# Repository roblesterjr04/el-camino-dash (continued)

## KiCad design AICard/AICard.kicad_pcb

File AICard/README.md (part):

# AI voice card

A **slot card** for the DigiDash rev 2 board: **80 × 60 mm**, standing on edge in a 2×15 slot, its right-angle header on the
bottom edge (`docs/hardware/accessory_ports.md`, rev 2 section). Requirements and design:
[`docs/hardware/ai_card.md`](../docs/hardware/ai_card.md). Firmware: [`firmware/ai_card/`](../firmware/ai_card/README.md)
(this card's ESP32-S3) and [`firmware/ai_agent/`](../firmware/ai_agent/README.md) (the assistant on the compute module).
It goes in **any slot**. On it:
- an **ESP32-S3-WROOM-1U-N16R8** (16 MB flash, 8 MB octal PSRAM; the IPEX version, because the radio is not used): CAN node,
  the I2S rail as a slave (microphone in, voice out), the wake word, the compute module's power switch
- a **2 × 20 female socket** (2.54 mm, 8.5 mm insulator) for the **compute module**, a Raspberry-Pi-header Linux board
  (reference: Radxa Zero 3W 8 GB with eMMC), held by two M2.5 standoffs
- a **TPS54560B buck** making the module's 5 V from **AUX 12 V** (slot pins 25–30), switched by the ESP32 through a P-FET
  (fail-safe: off whenever the ESP32 is off), with 470 µF bulk and a 220k / 47k sense of the AUX 12 V input
- a **74LVC125** that drives the rail's **RET** line only while the audio card grants it (enable pulled to *off*), 33 Ω in series
- an **MCP2562** CAN transceiver and an **AP7361C-33** 3.3 V regulator, both from the slot's 5 V
- **USB-C** (left edge) to the ESP32-S3's native USB, **BOOT** and **RESET** buttons, a **debug serial** header, two LEDs
  (module running, microphone open) and a **10k NTC** read by the ESP32

CAN node from its slot (`0x14 + (slot − 1)`), product `0x0007`. Firmware: `firmware/ai_card/`.

> ## Measure the compute module before ordering
>
> The module's size, header position and mounting holes on this card are **provisional**: they follow the Raspberry Pi Zero
> format, not a module in hand. The header map itself is the Raspberry Pi standard. Check, and edit the constants,
> then re-run the generators (see [Regenerating](#regenerating)):
>
> 1. **Pin 1 end and orientation of the header.** `J2_PIN1` in `generate/gen_pcb.py` (pin 1 at the left end, odd pins in the
>    upper row). If the module's pin 1 is at the other end the 5 V pins (2, 4) move to the other side of the card.
> 2. **Module outline** `MOD_X0, MOD_Y0, MOD_W, MOD_H` (65 × 30 mm, header 5 mm in from its lower edge). Nothing taller than
>    about 7 mm may stand inside it (the 470 µF is outside); check the module's bottom-side parts against the 8.5 mm socket.
> 3. **Mounting holes** `MOUNT_HOLES` (two of the module's far corners, 3.5 mm in; M2.5, 2.7 mm holes). Fit the standoffs
>    before judging: a 2×20 socket alone will walk out of a vibrating dash.
> 4. **Which header pins the module really uses** (`HEADER_NETS` in `generate/gen_sch.py`): UART on 8 / 10, ALIVE on 29,
>    SHUTDOWN_REQ on 31, ATTN on 33. Check that the module **accepts its 5 V supply on header pins 2 / 4** (it does on a Pi
>    Zero; confirm for the module in hand, and that nothing else powers it: no USB-C power while it sits on the card), which UART
>    pins 8 / 10 are on it and the device-tree overlay that enables it (`[link] port` in the agent's config), and that the GPIOs are
>    3.3 V.
> 5. **Height:** 8.5 mm socket + module + its heatsink must stay under the **20 mm** parts-side limit.
> 6. **Power:** the module's idle and peak current from the bench (the buck is 5 A; the design assumes 3 A peak).

| Files | |
| --- | --- |
| `AICard.kicad_sch` / `.kicad_pcb` / `.kicad_pro` | The card: 80 × 60 mm, 4 layers, parts on the front only. Generated with KiCad 7.0.11; the files were upgraded to KiCad 10 format on 2026-11-22 |
| `AICard_BOM.csv` | Bill of materials (`generate/gen_bom.py`) |
| `generate/` | `gen_sch.py`, `gen_pcb.py`, `gen_bom.py`, `drc.py`, `sexp.py`; `refs.json` is written by `gen_sch.py`. Copied from `LTECard/generate/` and adapted. Every footprint is stock KiCad, so there is no `.pretty` library |

## What's on it

```
AUX 12 V (pins 25-27) ─ 3 × 2.2 µF 100 V ─ TPS54560B (400 kHz) ─ 6.8 µH ─ MOD_5V ─┬─ 3 × 47 µF
AUX GND  (pins 28-30) ─────── all of the buck's grounds ─┘                         └─ 470 µF ─ socket pins 2, 4 (5 V)
                              socket GND pins (6, 9, 14, 20, 25, 30, 34, 39) = AUX_GND
AUX 12 V ─ 220k / 47k ─ GPIO5 (AUX present: the buck's INPUT; its output is off until the firmware has seen this)
Enable:  AUX12 ─ Q1 (P-FET) ─ 442k / 90.9k divider (starts at ~6.5 V, 5.1 V zener) ─ buck EN
         Q1 gate: 47k to AUX12, 47k to Q2; Q2 (N-FET) gate: GPIO11 through 1k, 100k pull-down. ESP32 off / in reset / unpowered = buck off
+5 V (pins 1, 2) ─ AP7361C-33 ─ +3V3 ─ ESP32-S3, MCP2562 VIO, 74LVC125, thermistor divider
ESP32-S3 UART1  TX GPIO41 ─ 1k ─► module RXD (socket 10)     RX GPIO42 ◄─ 1k ─ module TXD (socket 8)
         SHUT GPIO12 ─ 1k ─► socket 31   ALIVE GPIO13 ◄─ 1k ─ socket 29   ATTN GPIO14 ◄─► 1k ─ socket 33   (100k pull-downs on the ESP32 side)
I2S rail (slave): slot 15 BCK ─ 100 R ─ GPIO6   16 WS ─ 100 R ─ GPIO7   17 MIC ─ 100 R ─ GPIO15
         GPIO16 (RET data) ─► 74LVC125 gate 1 (/OE = GPIO17, 100k pull-up: off at power-up) ─ 33 R ─► slot 18 RET
CAN: GPIO9 TX / GPIO10 RX ── MCP2562 (VDD 5 V, VIO 3.3 V, STBY low, no termination) ── slot pins 5 / 6
Slot ID (pin 11): 10k to 3.3 V here, the slot's resistor to GND on the main board ──► GPIO4 (ADC1)
USB-C D+ / D- ── USBLC6-2SC6 ── GPIO20 / GPIO19 (native USB); CC1 / CC2 5.1k to GND; VBUS only to the clamp
```

### ESP32-S3 pins

| GPIO | Function | GPIO | Function |
| --- | --- | --- | --- |
| 41 / 42 | UART1 TX / RX to the module | 9 / 10 | CAN TX / RX (through 1k) |
| 11 | BUCK_ON (module's buck enable) | 4 | Slot ID (ADC1_CH3) |
| 12 | SHUTDOWN_REQ out | 5 | AUX 12 V present (ADC1_CH4): 2.1 V at 12 V |
| 13 | ALIVE in | 8 | NTC (ADC1_CH7) |
| 14 | ATTN (spare) | 1 / 2 | LED module / LED microphone |
| 6 / 7 / 15 | rail BCK / WS / MIC in | 19 / 20 | USB D− / D+ |
| 16 / 17 | RET data out / RET buffer enable (low = drive) | 43 / 44 | TXD0 / RXD0, debug serial J3 |
| 0 | BOOT button (strap) | EN | RESET button, 10k / 1 µF |

Not used: the strapping pins GPIO3, 45, 46 (and GPIO0 except for BOOT), the flash and octal-PSRAM pins GPIO26–37, GPIO18, 21, 38–40, 47, 48.
`firmware/ai_card/src/ai_pins.h` repeats this table; keep them in step.

### Grounds: AUX GND is not GND

As on the LTE card: on the main board AUX GND meets GND only at NT1, so this card does **not** join them. The buck, the 470 µF and the
module's return are on AUX_GND (its own pours on F, In2 and B over the buck area); the ESP32, CAN, USB, the rail and the 3.3 V
regulator are on GND (In1 is a solid GND plane under the whole card). Only logic crosses, through 1k resistors. On the bench a card
powered without the main board needs AUX GND and GND joined at the supply.

## Slot connector (J1)

| Pins | Signal | Used |
| --- | --- | --- |
| 1 / 2 | +5 V | ESP32-S3, CAN, 3.3 V regulator |
| 3 / 4, 7, 19 / 20 | GND | logic ground |
| 5 / 6 | CANH / CANL | MCP2562 |
| 11 | slot ID | 10k to 3.3 V, GPIO4 |
| 15 / 16 / 17 | I2S BCK / WS / MIC | inputs through 100 Ω |
| 18 | I2S RET | 74LVC125 and 33 Ω: a 3-state output, never driven without the audio card's grant |
| 25 / 26 / 27 | AUX 12 V | the module's buck |
| 28 / 29 / 30 | AUX GND | the buck and the module's return |
| 8, 9, 10, 12–14, 21–24 | switched / constant 12 V, 3.3 V, WAKE, LAMP, REV, audio bus, MCLK | not connected |

| Other connectors | | |
| --- | --- | --- |
| J2 | Compute module, 2 × 20 female, 8.5 mm | Raspberry Pi 40-pin map: 5 V on 2 / 4, GND on 6 / 9 / 14 / 20 / 25 / 30 / 34 / 39, UART 8 / 10, ALIVE 29, SHUTDOWN_REQ 31, ATTN 33 |
| J3 | debug serial, 1 × 3 right angle, left edge | 1 GND, 2 TX0 (to the adapter's RX), 3 RX0. 3.3 V logic, not a supply |
| J4 | USB-C (GCT USB4105, horizontal), left edge | native USB: flash and serial console. The card is powered from the slot |
| SW1 / SW2 | RESET / BOOT, top edge | Flash: hold BOOT, tap RESET (only needed if the USB-JTAG is not answering) |
| H1 / H2 | M2.5 holes for the module's standoffs | provisional positions |

## Board

- **Outline:** 80 × 60 mm, no card-mounting holes (the slot and the case hold it); two M2.5 holes for the module only.
- **Slot header (J1):** placed exactly as on the audio and LTE cards (`PinHeader_2x15_P2.54mm_Horizontal`, pin 1 17.78 mm right of
  the centre, the pins counting to the left, its body on the bottom edge); `gen_pcb.py` checks the orientation from the pads.
- **Middle:** the module's socket across the card (pin 1 at the left); the module hangs over the upper half of the card,
  8.5 mm up. **Under it** (all lower than 7 mm): the ESP32-S3-1U at the left, the buttons and thermistor, LEDs, resistors.
- **Left edge:** LEDs, USB-C (plug facing out), the debug header (pins out of the edge). **Top edge:** RESET / BOOT.
- **Bottom:** the buck by the AUX pins (25–30), the 470 µF beside it (10 mm tall, so outside the module's shadow), the RET
  buffer by the rail pins (15–18), the CAN transceiver and the 3.3 V regulator by pins 1–6.
- **Back:** nothing (it faces the next card; the 2.5 mm allowance is not used).
- **Layers:** F signal, In1 solid GND plane, In2 signal / pours, B signal. 0.2 mm tracks, 0.13 mm clearance, 0.6 / 0.3 mm vias.
  Net classes as on the LTE card: Power 0.3 mm (GND, +5V, +3V3); Aux 0.8 mm / 0.2 mm (AUX12); Mod5V 1.0 mm / 0.2 mm (MOD_5V); AuxGnd 0.8 mm / 0.2 mm
  (AUX_GND); Switch 1.0 mm / 0.2 mm (BUCK_SW).
- **No antenna:** the -1U module's IPEX connector is left empty; Wi-Fi is the compute module's (its own antenna).

## Status

**Schematic: done** (78 parts). **PCB: placed and routed** by `gen_pcb.py` (2026-10-04): 80 × 60 mm, 4 layers, 78 footprints,
747 tracks and 635 vias (558 of them GND stitching), Freerouting 2.4.1 plus the script's own steps, no hand edits.
DRC (KiCad 7.0.11): **0 errors, 0 unconnected.** Warnings only: 78 "library not in the library table" (the project has no
`fp-lib-table`, as on the LTE card), 20 silkscreen past the edge (J1, J3 and J4 stick out of the outline on purpose), 3 silkscreen
clipped by mask, 2 silkscreen overlaps. **Not ordered.** Merged to main on 2026-11-22; the BOM CSV was regenerated then (the committed one predated the
220k / 47k AUX sense divider and listed 22k / 33k, which would have put about 7 V on GPIO5). Fab files: `fab/` (`python3 ../tools/fab_export.py AICard`).

**KiCad 10 pass (2026-11-22).** Both files upgraded with `kicad-cli sch upgrade` / `pcb upgrade`; nothing on the board moved.
- **ERC** (KiCad 10.0.2): 0 errors, 409 warnings: 396 endpoints off grid, 13 library notes (the `AICard` symbol nickname is not in a
  library table; J4's and the LEDs' symbols differ from KiCad 10's copies).
- **DRC with the schematic parity check** (`generate/drc.py`, now kicad-cli as on the other cards): 0 errors, 0 unconnected.
  Warnings: 68 footprints differ from KiCad 10's library copies, 68 *Description* fields set in the schematic only, 20 silkscreen past
  the edge (J1, J3, J4, on purpose), 5 silkscreen over copper, 2 silkscreen overlaps. Parity otherwise clean: every part, value and net matches.
- **Mask dams:** `tools/mask_dams.py` narrowed J4's eight 0.5 mm-pitch signal pads to 0.28 mm (0.22 mm gaps); zones refilled.
- **AP7361C-33E pinout checked** against the Diodes datasheet: suffix E is SOT223 (ER is the reversed SOT223R), pin 1 IN, 2 GND
  (tab), 3 OUT, as drawn. ConsoleBoardRS uses the same part and pinout.
- **Power tracks** measured in the routed board (the 5 V pre-route was blocked and the router laid them): MOD_5V 1.0 mm on F.Cu
  and B.Cu (a 0.8 mm stub at a pad), AUX12 and AUX_GND 0.8 mm, BUCK_SW 1.0 mm, the slot +5 V 0.3 mm (it feeds only the ESP32 side).
- **Fab files** re-exported with KiCad 10 (`fab/`, inner layers now `.g1` / `.g2`, plus a JLC CPL).

What has **not** been checked, and what to do about it before ordering:
- **The compute module** (size, header end, mounting holes, which pins it powers from): see the box at the top.
- **The buck** is the main board's circuit with a smaller inductor and the 470 µF at the load; its loop was not simulated. Check L1's
  ratings (Isat ≥ 5 A, Irms ≥ 3 A) and the compensation with TI WEBENCH or a load-step test on the real module.
- **J4 (the GCT USB4105)**: its own locating hole is 0.194 mm from pad B12, so the project's minimum hole clearance is set to
  0.19 mm instead of 0.25 mm; confirm the fab's limit. Only the A4 / B9 VBUS contacts are wired (the others sit 4.8 mm away across the
  signal pads, and VBUS powers nothing here).
- **Thermal**: nothing has been measured; the design relies on the two-step throttle in the firmware (`docs/hardware/ai_card.md`).
- **AUX budget (changed on the main board after this card was drawn).** Since 2026-10-19 DigiDash2's AUX 12 V is sized for
  about **3 A for all slots together** (5 A fuse; it was 10 A). This card's 3 A peak at 5 V is about 1.4 A from 12 V, and the
  LTE card's modem buck about 1 A: both fit, with little margin. Measure the module's peak before adding another AUX user.
- **The module's UART on header pins 8 / 10** may be its Linux debug console (on Radxa Zero 3 boards it usually is, at
  1.5 Mbaud): either turn the console off in the module's image or move the link to another UART. Confirm on the module.
- **Slot numbering was fixed on the main board on 2026-10-19** (`accessory_ports.md`, Numbering). The card side did not change
  and J1 is placed as on the audio and LTE cards, so this card should mate; confirm in KiCad's 3D viewer with DigiDash2.
- **No PCBWay BOM yet** (`fab/pcbway/`, as on the other cards). Every part is SMD except J1–J3, which PCBWay can fit too.
- **Pin 1 of J1** against the main board's slot, and the USB-C and debug header against the case, in KiCad's 3D viewer.

## Regenerating

**The generators still write KiCad 7 format** (`gen_sch.py`, `gen_pcb.py`): after a regeneration run `kicad-cli sch upgrade` and
`kicad-cli pcb upgrade` on the two files, then `tools/mask_dams.py AICard` and `gen_pcb.py --fill`. `--fill` runs on KiCad 10's
Python (`$KIPY`); the full place-and-route has only been run on KiCad 7.

KiCad's stock libraries and `kicad-cli`, a Python with `pcbnew` and `numpy`, and Freerouting (Java; **2.4.1 needs Java 25** and
runs with `--gui.enabled=false`; 1.9.0 with Java 17+ also worked for the LTE card). This card was generated with KiCad
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
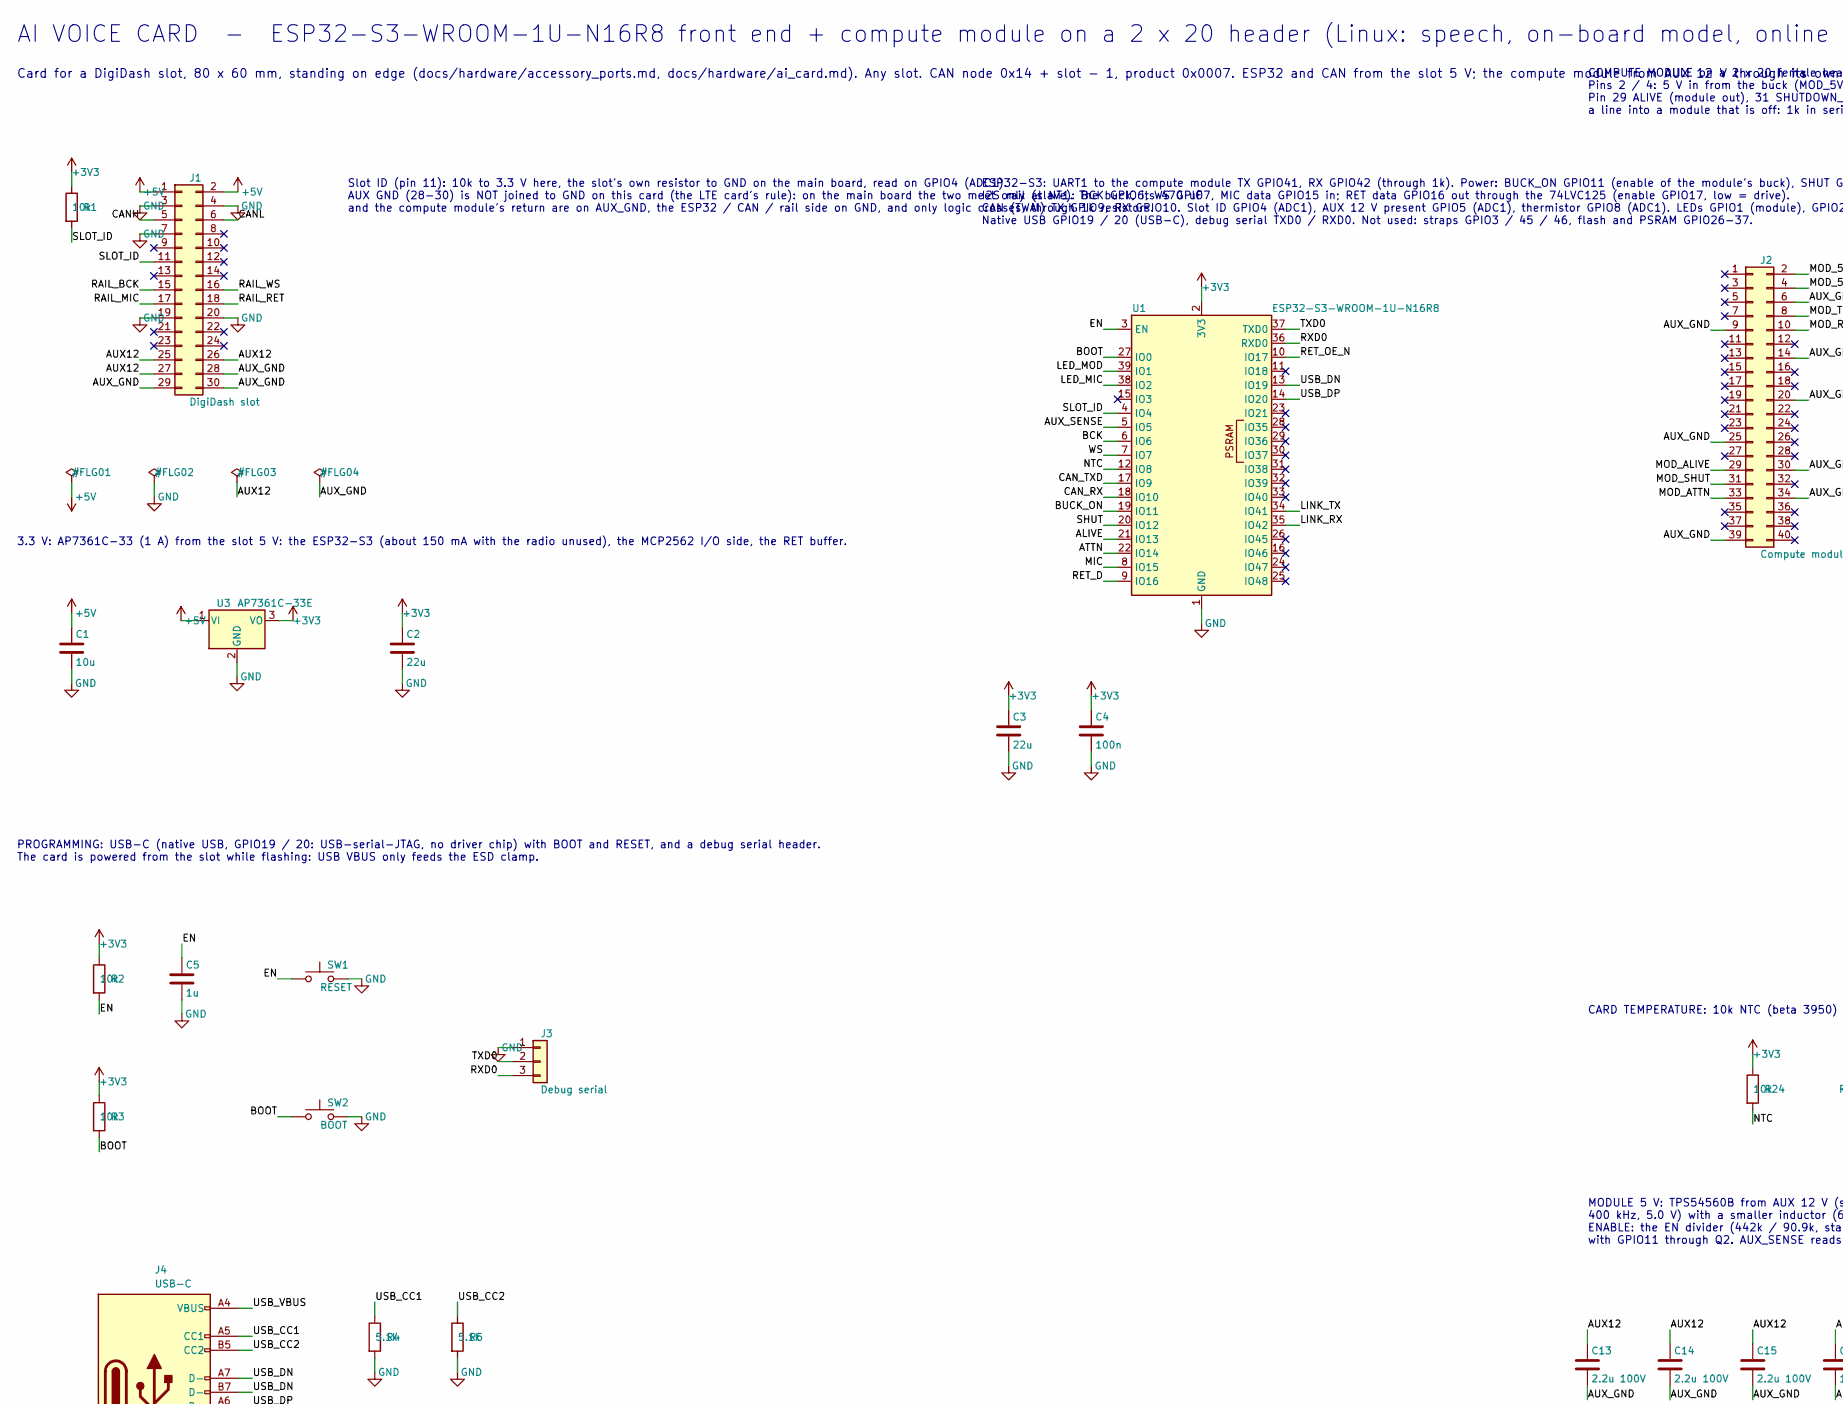
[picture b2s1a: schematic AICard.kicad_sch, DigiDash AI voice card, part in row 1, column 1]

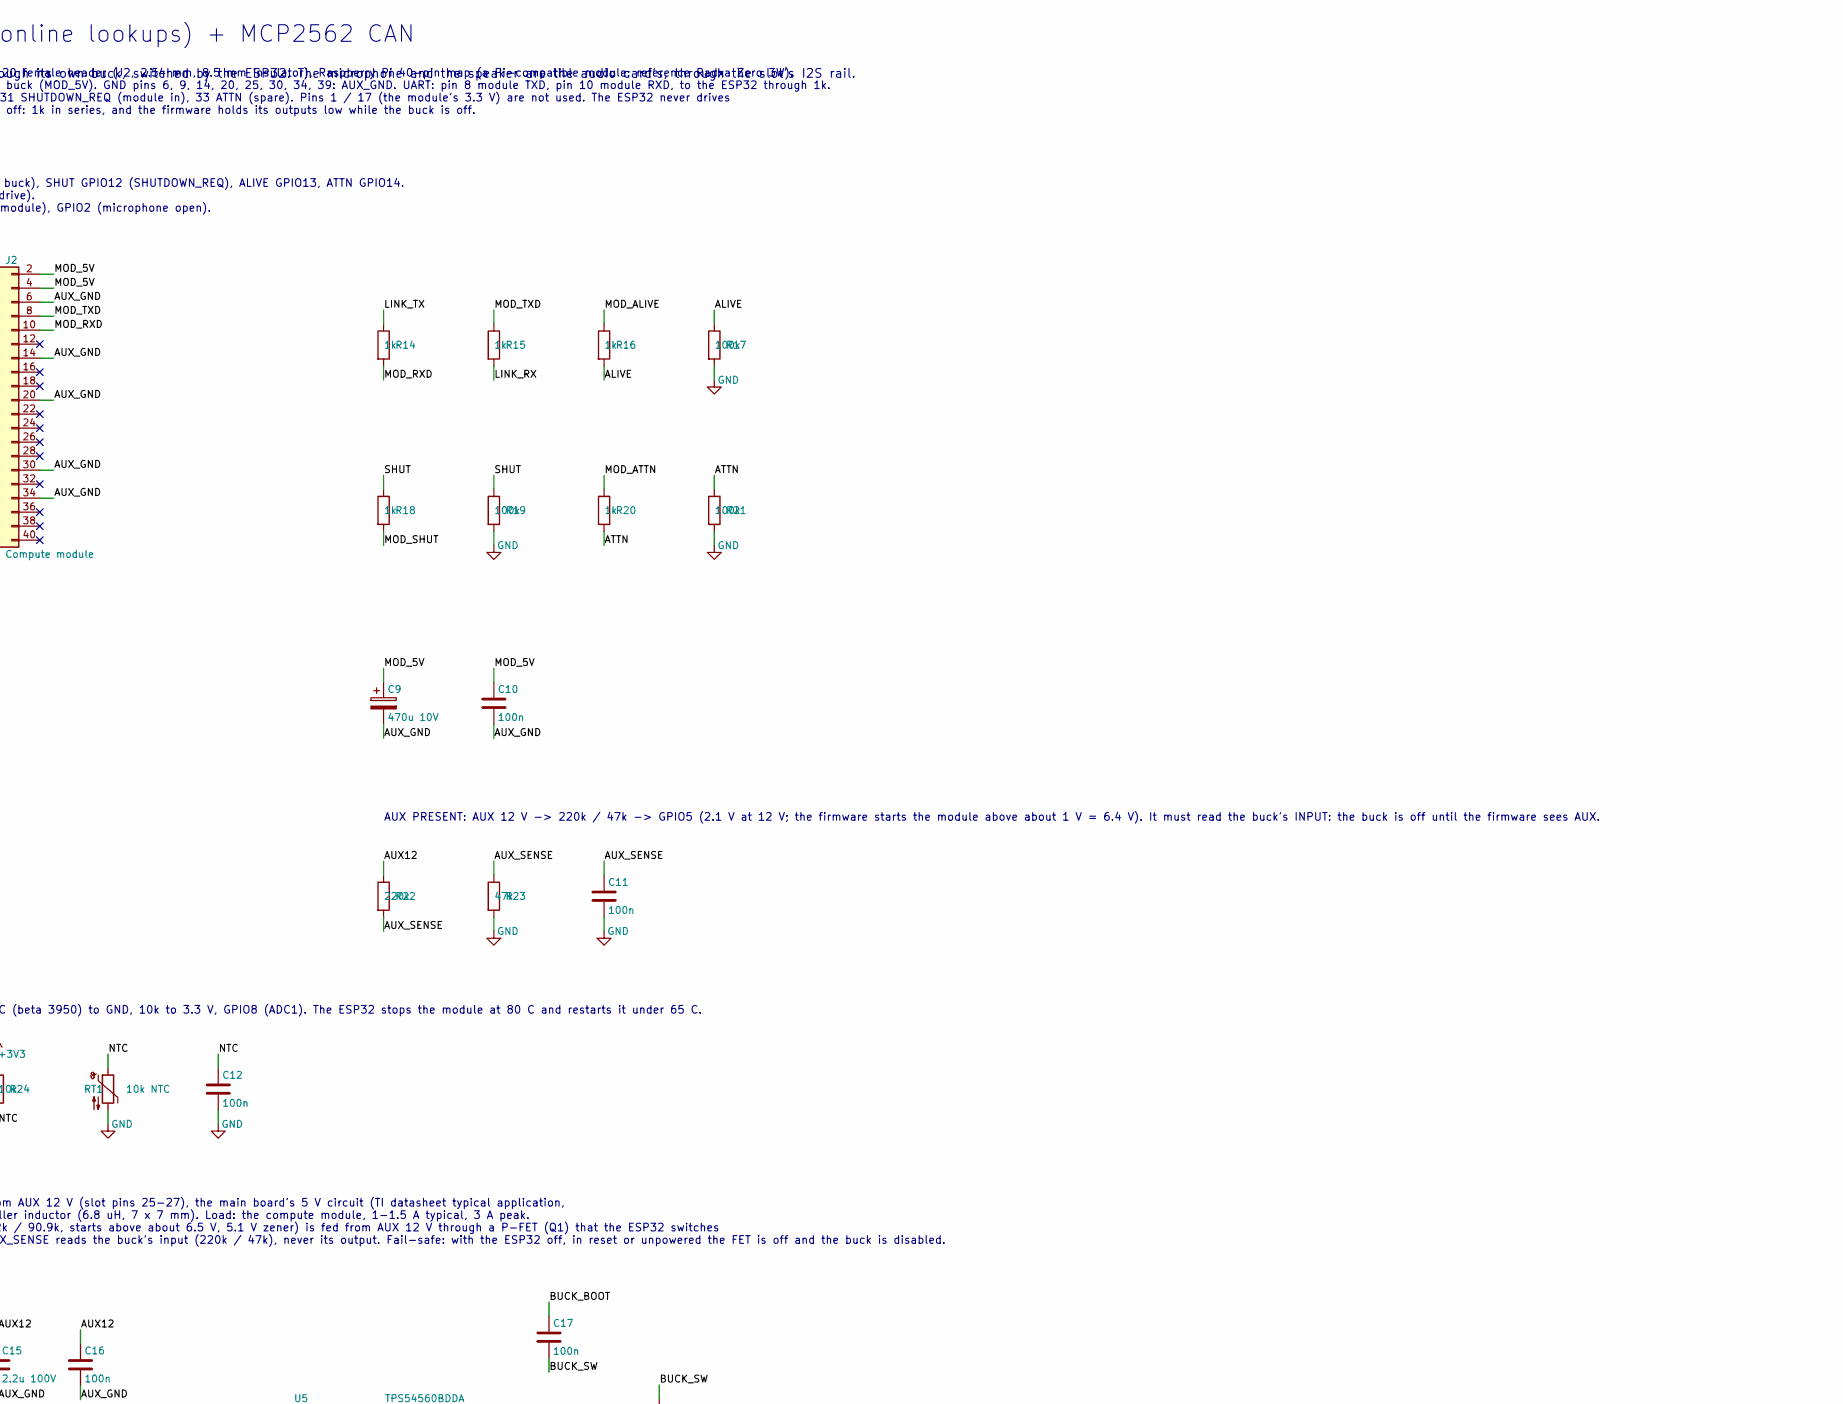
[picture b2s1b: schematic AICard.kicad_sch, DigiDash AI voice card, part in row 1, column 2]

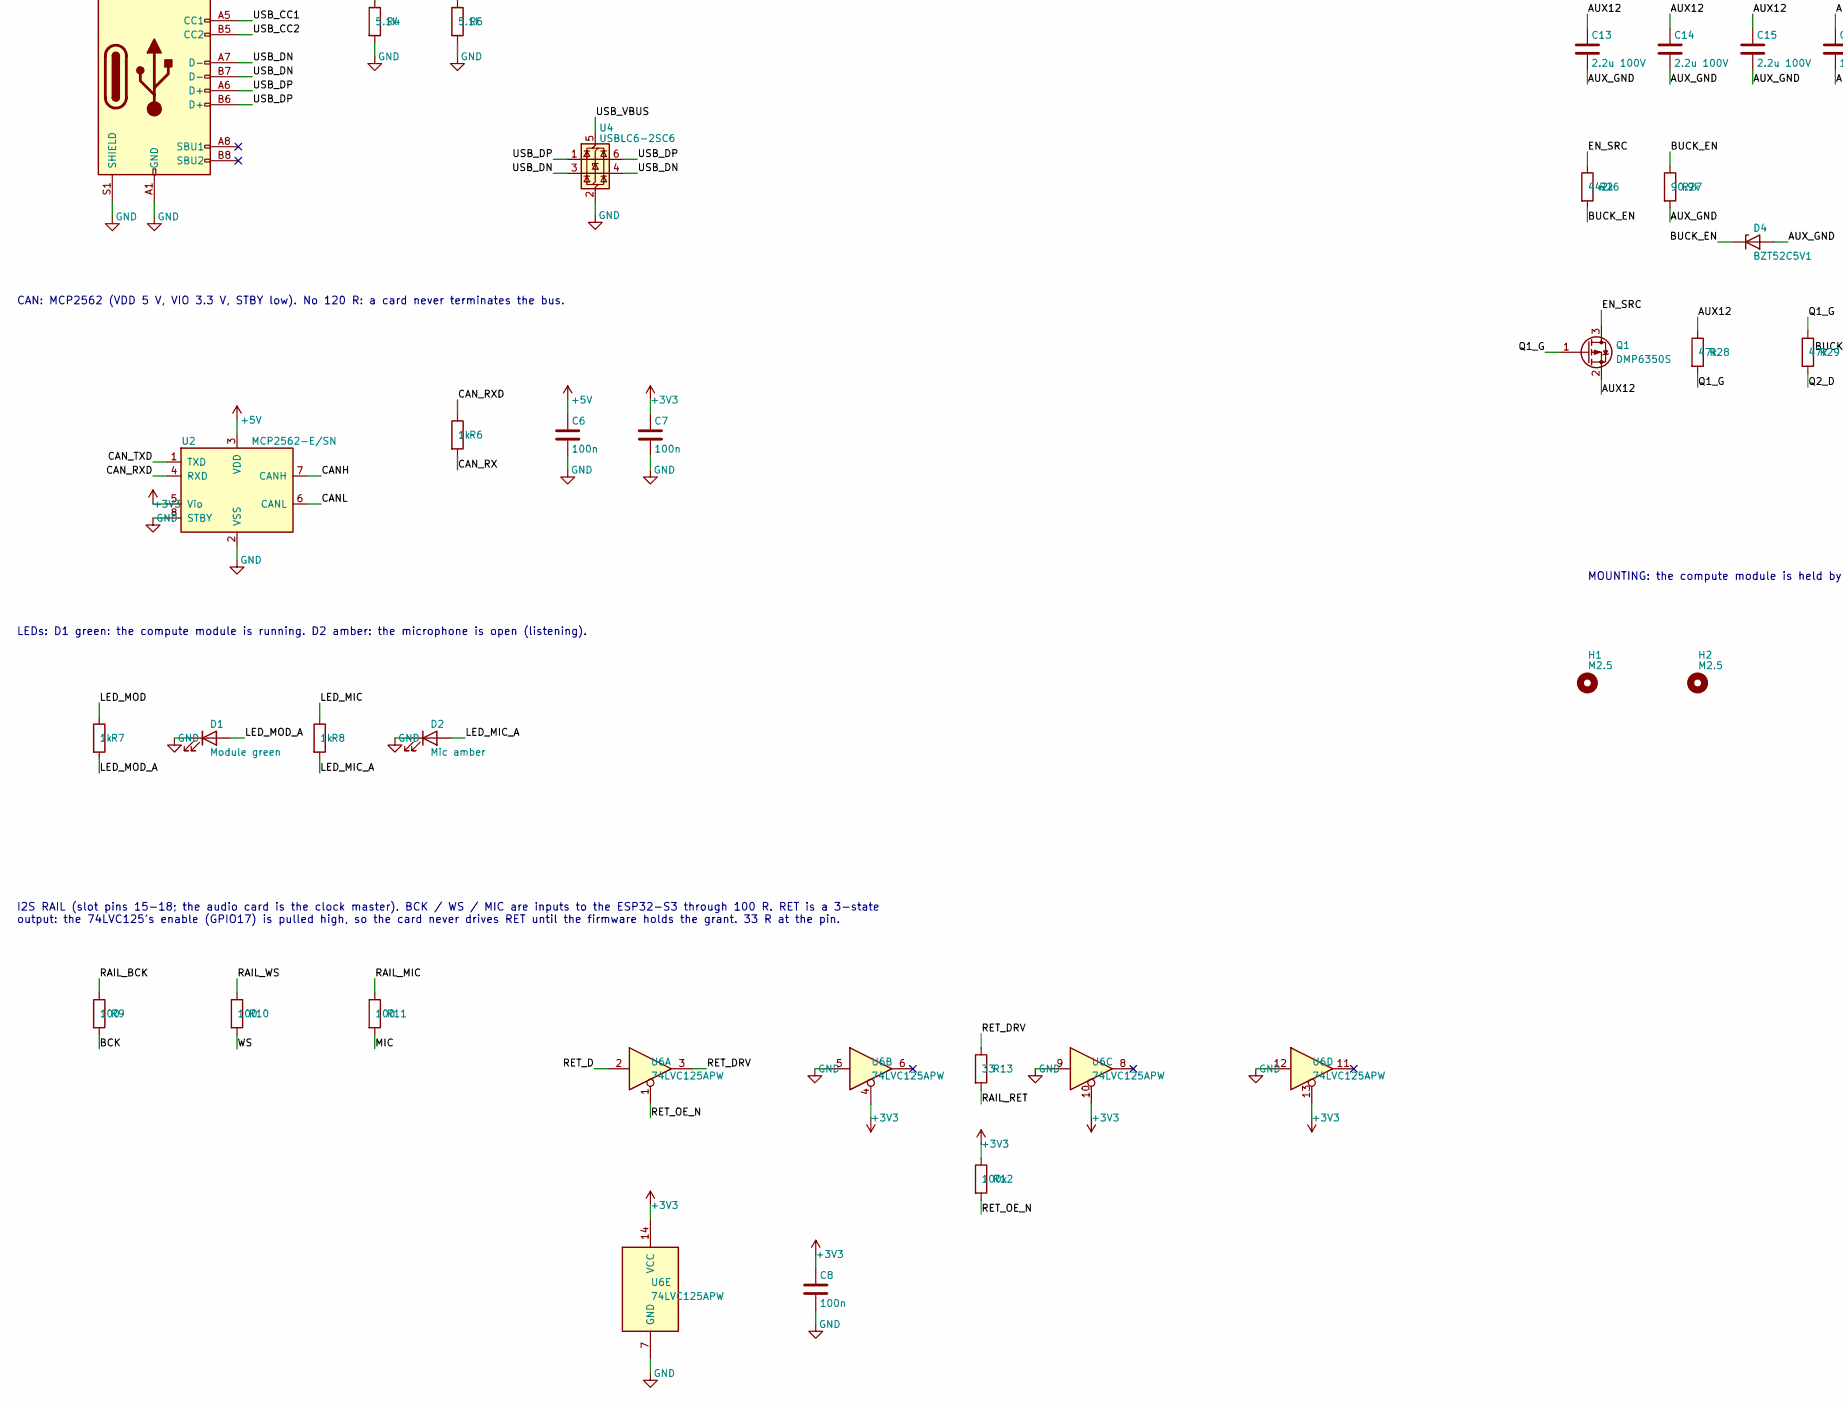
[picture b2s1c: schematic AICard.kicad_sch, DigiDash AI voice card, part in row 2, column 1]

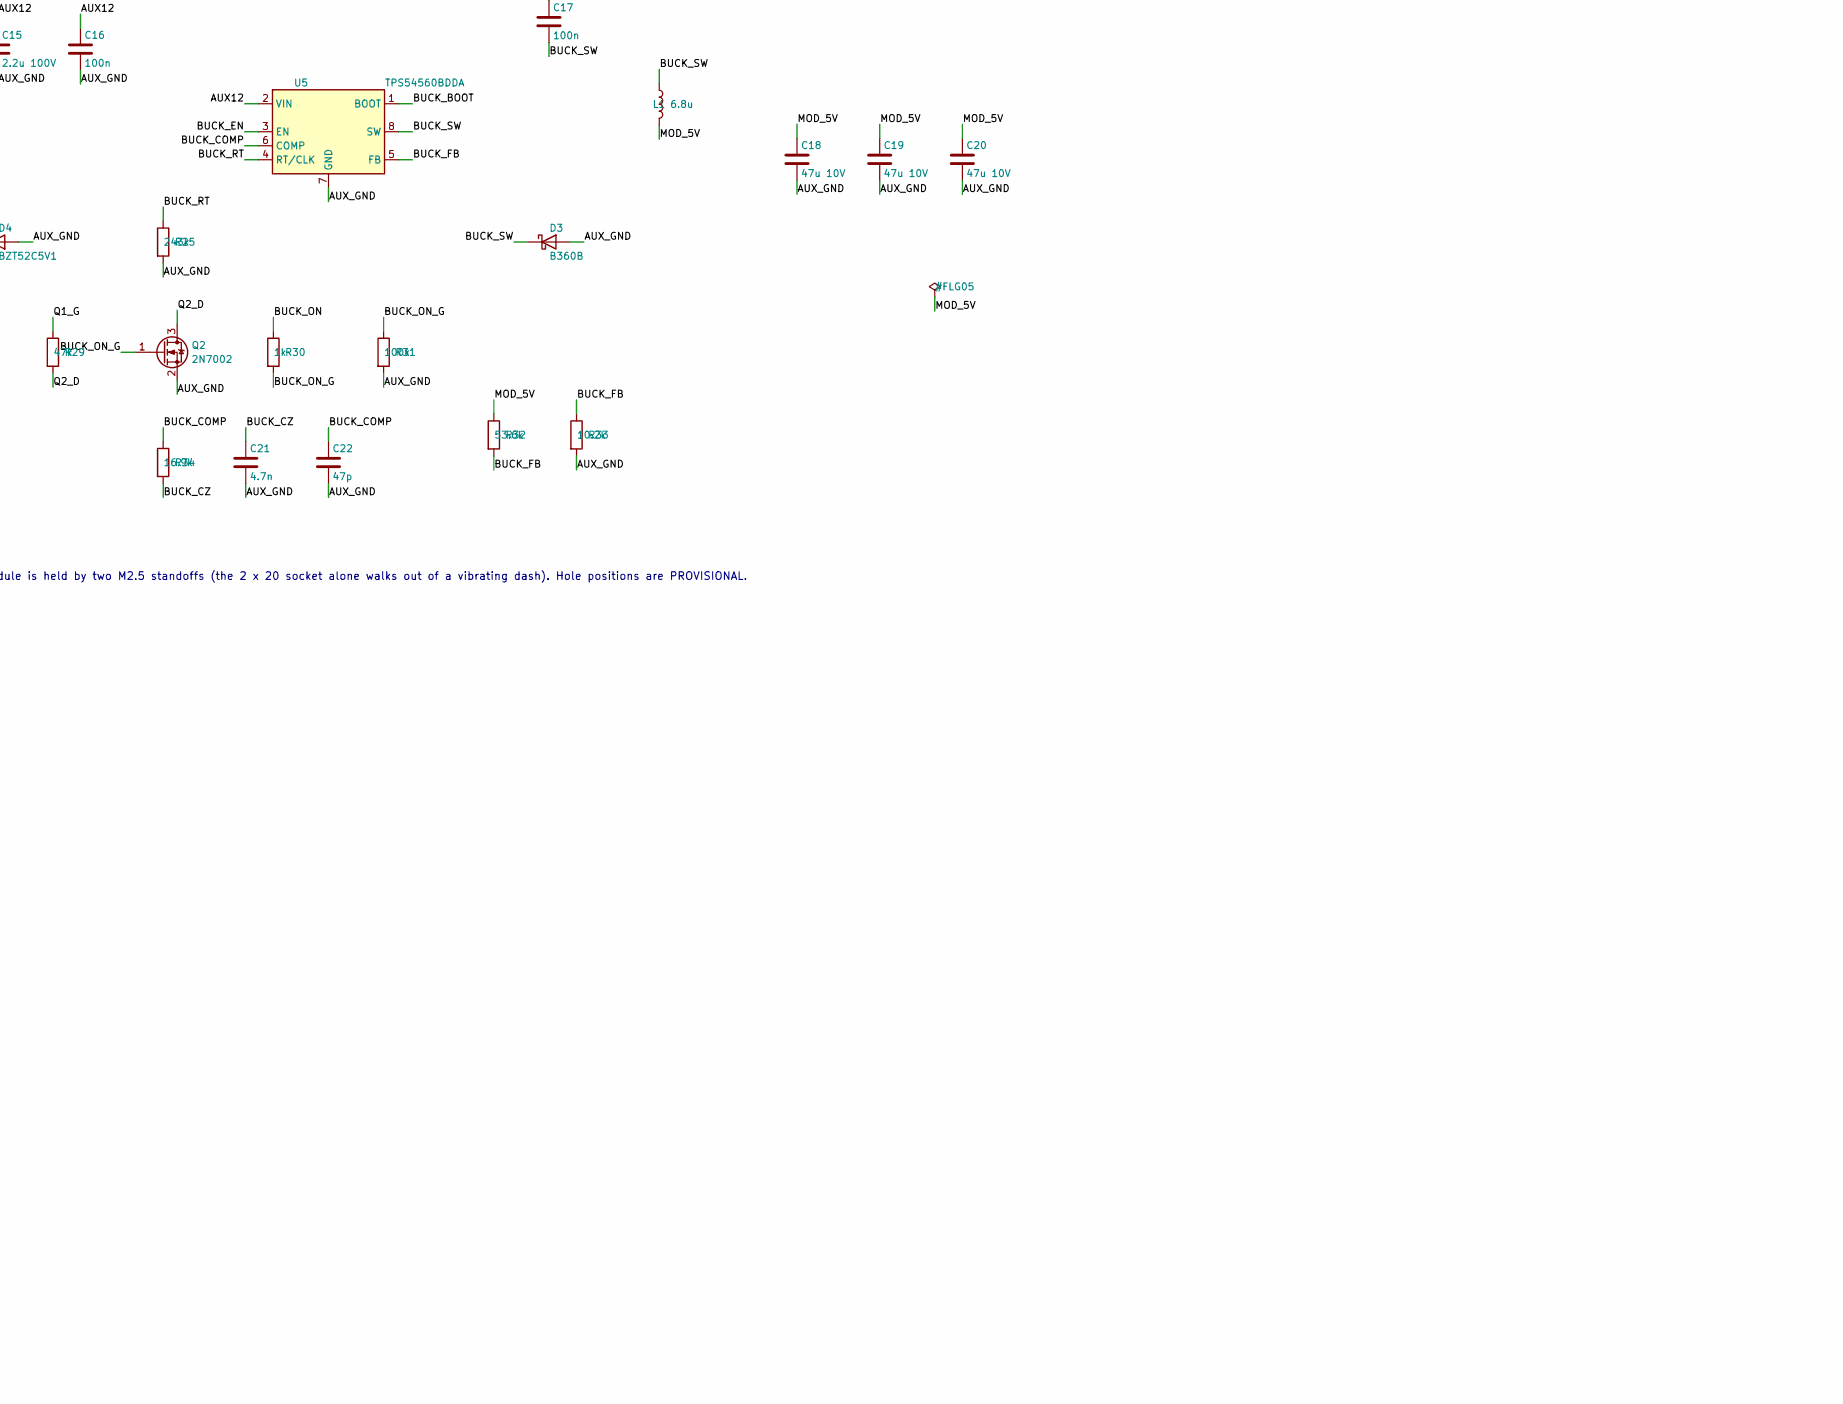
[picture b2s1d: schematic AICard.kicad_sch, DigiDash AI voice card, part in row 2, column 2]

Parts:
C1: 10u; C_0805_2012Metric
C2, C3: 22u; C_0805_2012Metric
C4, C6, C7, C8, C10, C11, C12, C17: 100n; C_0603_1608Metric
C5: 1u; C_0603_1608Metric
C9: 470u 10V; CP_Elec_8x10
C13, C14, C15: 2.2u 100V; C_1210_3225Metric
C16: 100n; C_0805_2012Metric
C18, C19, C20: 47u 10V; C_1210_3225Metric
C21: 4.7n; C_0603_1608Metric
C22: 47p; C_0603_1608Metric
D1: Module green; LED_0603_1608Metric
D2: Mic amber; LED_0603_1608Metric
D3: B360B; D_SMB
D4: BZT52C5V1; D_SOD-123
H1, H2: M2.5; MountingHole_2.7mm_M2.5
J1: DigiDash slot; PinHeader_2x15_P2.54mm_Horizontal
J2: Compute module; PinSocket_2x20_P2.54mm_Vertical
J3: Debug serial; PinHeader_1x03_P2.54mm_Horizontal
J4: USB-C; USB_C_Receptacle_GCT_USB4105-xx-A_16P_TopMnt_Horizontal
L1: 6.8u; L_Bourns_SRP7028A_7.3x6.6mm
Q1: DMP6350S; SOT-23
Q2: 2N7002; SOT-23
R1, R2, R3, R24: 10k; R_0603_1608Metric
R4, R5: 5.1k; R_0603_1608Metric
R6, R7, R8, R14, R15, R16, R18, R20, R30: 1k; R_0603_1608Metric
R9, R10, R11: 100; R_0603_1608Metric
R12, R17, R19, R21, R31: 100k; R_0603_1608Metric
R13: 33; R_0603_1608Metric
R22: 220k; R_0603_1608Metric
R23, R28, R29: 47k; R_0603_1608Metric
R25: 243k; R_0603_1608Metric
R26: 442k; R_0603_1608Metric
R27: 90.9k; R_0603_1608Metric
R32: 53.6k; R_0603_1608Metric
R33: 10.2k; R_0603_1608Metric
R34: 16.9k; R_0603_1608Metric
RT1: 10k NTC; R_0603_1608Metric
SW1: RESET; SW_SPST_PTS810
SW2: BOOT; SW_SPST_PTS810
U1: ESP32-S3-WROOM-1U-N16R8; ESP32-S3-WROOM-1U
U2: MCP2562-E/SN; SOIC-8_3.9x4.9mm_P1.27mm
U3: AP7361C-33E; SOT-223-3_TabPin2
U4: USBLC6-2SC6; SOT-23-6
U5: TPS54560BDDA; TI_SO-PowerPAD-8_ThermalVias
U6: 74LVC125APW; TSSOP-14_4.4x5mm_P0.65mm

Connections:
+3V3: C2.1, C3.1, C4.1, C7.1, C8.1, R1.1, R2.1, R3.1, R12.1, R24.1, U1.2 (3V3), U2.5 (Vio), U3.3 (VO), U6.4, U6.10, U6.13, U6.14 (VCC)
+5V: C1.1, C6.1, J1.1, J1.2, U2.3 (VDD), U3.1 (VI)
/ALIVE: R16.2, R17.1, U1.21 (IO13)
/ATTN: R20.2, R21.1, U1.22 (IO14)
/AUX12: C13.1, C14.1, C15.1, C16.1, J1.25, J1.26, J1.27, Q1.2 (S), R22.1, R28.1, U5.2 (VIN)
/AUX_GND: C9.2, C10.2, C13.2, C14.2, C15.2, C16.2, C18.2, C19.2, C20.2, C21.2, C22.2, D3.2 (A), D4.2 (A), J1.28, J1.29, J1.30, J2.6, J2.9, J2.14, J2.20, J2.25, J2.30, J2.34, J2.39, Q2.2 (S), R25.2, R27.2, R31.2, R33.2, U5.7 (GND), U5.9 (GND)
/AUX_SENSE: C11.1, R22.2, R23.1, U1.5 (IO5)
/BCK: R9.2, U1.6 (IO6)
/BOOT: R3.2, SW2.1, U1.27 (IO0)
/BUCK_BOOT: C17.1, U5.1 (BOOT)
/BUCK_COMP: C22.1, R34.1, U5.6 (COMP)
/BUCK_CZ: C21.1, R34.2
/BUCK_EN: D4.1 (K), R26.2, R27.1, U5.3 (EN)
/BUCK_FB: R32.2, R33.1, U5.5 (FB)
/BUCK_ON: R30.1, U1.19 (IO11)
/BUCK_ON_G: Q2.1 (G), R30.2, R31.1
/BUCK_RT: R25.1, U5.4 (RT/CLK)
/BUCK_SW: C17.2, D3.1 (K), L1.1, U5.8 (SW)
/CANH: J1.5, U2.7 (CANH)
/CANL: J1.6, U2.6 (CANL)
/CAN_RX: R6.2, U1.18 (IO10)
/CAN_RXD: R6.1, U2.4 (RXD)
/CAN_TXD: U1.17 (IO9), U2.1 (TXD)
/EN: C5.1, R2.2, SW1.1, U1.3 (EN)
/EN_SRC: Q1.3 (D), R26.1
/LED_MIC: R8.1, U1.38 (IO2)
/LED_MIC_A: D2.2 (A), R8.2
/LED_MOD: R7.1, U1.39 (IO1)
/LED_MOD_A: D1.2 (A), R7.2
/LINK_RX: R15.2, U1.35 (IO42)
/LINK_TX: R14.1, U1.34 (IO41)
/MIC: R11.2, U1.8 (IO15)
/MOD_5V: C9.1, C10.1, C18.1, C19.1, C20.1, J2.2, J2.4, L1.2, R32.1
/MOD_ALIVE: J2.29, R16.1
/MOD_ATTN: J2.33, R20.1
/MOD_RXD: J2.10, R14.2
/MOD_SHUT: J2.31, R18.2
/MOD_TXD: J2.8, R15.1
/NTC: C12.1, R24.2, RT1.1, U1.12 (IO8)
/Q1_G: Q1.1 (G), R28.2, R29.1
/Q2_D: Q2.3 (D), R29.2
/RAIL_BCK: J1.15, R9.1
/RAIL_MIC: J1.17, R11.1
/RAIL_RET: J1.18, R13.2
/RAIL_WS: J1.16, R10.1
/RET_D: U1.9 (IO16), U6.2
/RET_DRV: R13.1, U6.3
/RET_OE_N: R12.2, U1.10 (IO17), U6.1
/RXD0: J3.3, U1.36 (RXD0)
/SHUT: R18.1, R19.1, U1.20 (IO12)
/SLOT_ID: J1.11, R1.2, U1.4 (IO4)
/TXD0: J3.2, U1.37 (TXD0)
/USB_CC1: J4.A5 (CC1), R4.1
/USB_CC2: J4.B5 (CC2), R5.1
/USB_DN: J4.A7 (D-), J4.B7 (D-), U1.13 (IO19), U4.3 (I/O2), U4.4 (I/O2)
/USB_DP: J4.A6 (D+), J4.B6 (D+), U1.14 (IO20), U4.1 (I/O1), U4.6 (I/O1)
/USB_VBUS: J4.A4 (VBUS), J4.A9 (VBUS), J4.B4 (VBUS), J4.B9 (VBUS), U4.5 (VBUS)
/WS: R10.2, U1.7 (IO7)
GND: C1.2, C2.2, C3.2, C4.2, C5.2, C6.2, C7.2, C8.2, C11.2, C12.2, D1.1 (K), D2.1 (K), J1.3, J1.4, J1.7, J1.19, J1.20, J3.1, J4.A1 (GND), J4.A12 (GND), J4.B1 (GND), J4.B12 (GND), J4.S1 (SHIELD), R4.2, R5.2, R17.2, R19.2, R21.2, R23.2, RT1.2, SW1.2, SW2.2, U1.1 (GND), U1.40 (GND), U1.41 (GND), U2.2 (VSS), U2.8 (STBY), U3.2 (GND), U4.2 (GND), U6.5, U6.7 (GND), U6.9, U6.12

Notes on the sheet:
Slot ID (pin 11): 10k to 3.3 V here, the slot's own resistor to GND on the main board, read on GPIO4 (ADC1). AUX GND (28-30) is NOT joined to GND on this card (the LTE card's rule): on the main board the two meet only at NT1. The buck, its 470 uF and the compute module's return are on AUX_GND, the 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
AI VOICE CARD - ESP32-S3-WROOM-1U-N16R8 front end + compute module on a 2 x 20 header (Linux: speech, on-board model, online lookups) + MCP2562 CAN
COMPUTE MODULE on a 2 x 20 female header (J2, 2.54 mm, 8.5 mm insulator), Raspberry Pi 40-pin map (a Pi-compatible module: reference Radxa Zero 3W). Pins 2 / 4: 5 V in from the buck (MOD_5V). GND pins 6, 9, 14, 20, 25, 30, 34, 39: AUX_GND. UART: pin 8 module TXD, pin 10 module RXD, to the ESP32 thr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
CAN: MCP2562 (VDD 5 V, VIO 3.3 V, STBY low). No 120 R: a card never terminates the bus.
LEDs: D1 green: the compute module is running. D2 amber: the microphone is open (listening).
PROGRAMMING: USB-C (native USB, GPIO19 / 20: USB-serial-JTAG, no driver chip) with BOOT and RESET, and a debug serial header. The card is powered from the slot while flashing: USB VBUS only feeds the ESD clamp.
Card for a DigiDash slot, 80 x 60 mm, standing on edge (docs/hardware/accessory_ports.md, docs/hardware/ai_card.md). Any slot. CAN node 0x14 + slot - 1, product 0x0007. ESP32 and CAN from the slot 5 V; the compute module from AUX 12 V through its own buck, switched by the ESP32. The microphone and 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
3.3 V: AP7361C-33 (1 A) from the slot 5 V: the ESP32-S3 (about 150 mA with the radio unused), the MCP2562 I/O side, the RET buffer.
ESP32-S3: UART1 to the compute module TX GPIO41, RX GPIO42 (through 1k). Power: BUCK_ON GPIO11 (enable of the module's buck), SHUT GPIO12 (SHUTDOWN_REQ), ALIVE GPIO13, ATTN GPIO14. I2S rail (slave): BCK GPIO6, WS GPIO7, MIC data GPIO15 in; RET data GPIO16 out through the 74LVC125 (enable GPIO17, lo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
I2S RAIL (slot pins 15-18; the audio card is the clock master). BCK / WS / MIC are inputs to the ESP32-S3 through 100 R. RET is a 3-state output: the 74LVC125's enable (GPIO17) is pulled high, so the card never drives RET until the firmware holds the grant. 33 R at the pin.
MODULE 5 V: TPS54560B from AUX 12 V (slot pins 25-27), the main board's 5 V circuit (TI datasheet typical application, 400 kHz, 5.0 V) with a smaller inductor (6.8 uH, 7 x 7 mm). Load: the compute module, 1-1.5 A typical, 3 A peak. ENABLE: the EN divider (442k / 90.9k, starts above about 6.5 V, 5.1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
MOUNTING: the compute module is held by two M2.5 standoffs (the 2 x 20 socket alone walks out of a vibrating dash). Hole positions are PROVISIONAL.
CARD TEMPERATURE: 10k NTC (beta 3950) to GND, 10k to 3.3 V, GPIO8 (ADC1). The ESP32 stops the module at 80 C and restarts it under 65 C.
AUX PRESENT: AUX 12 V -> 220k / 47k -> GPIO5 (2.1 V at 12 V; the firmware starts the module above about 1 V = 6.4 V). It must read the buck's INPUT: the buck is off until the firmware sees AUX.

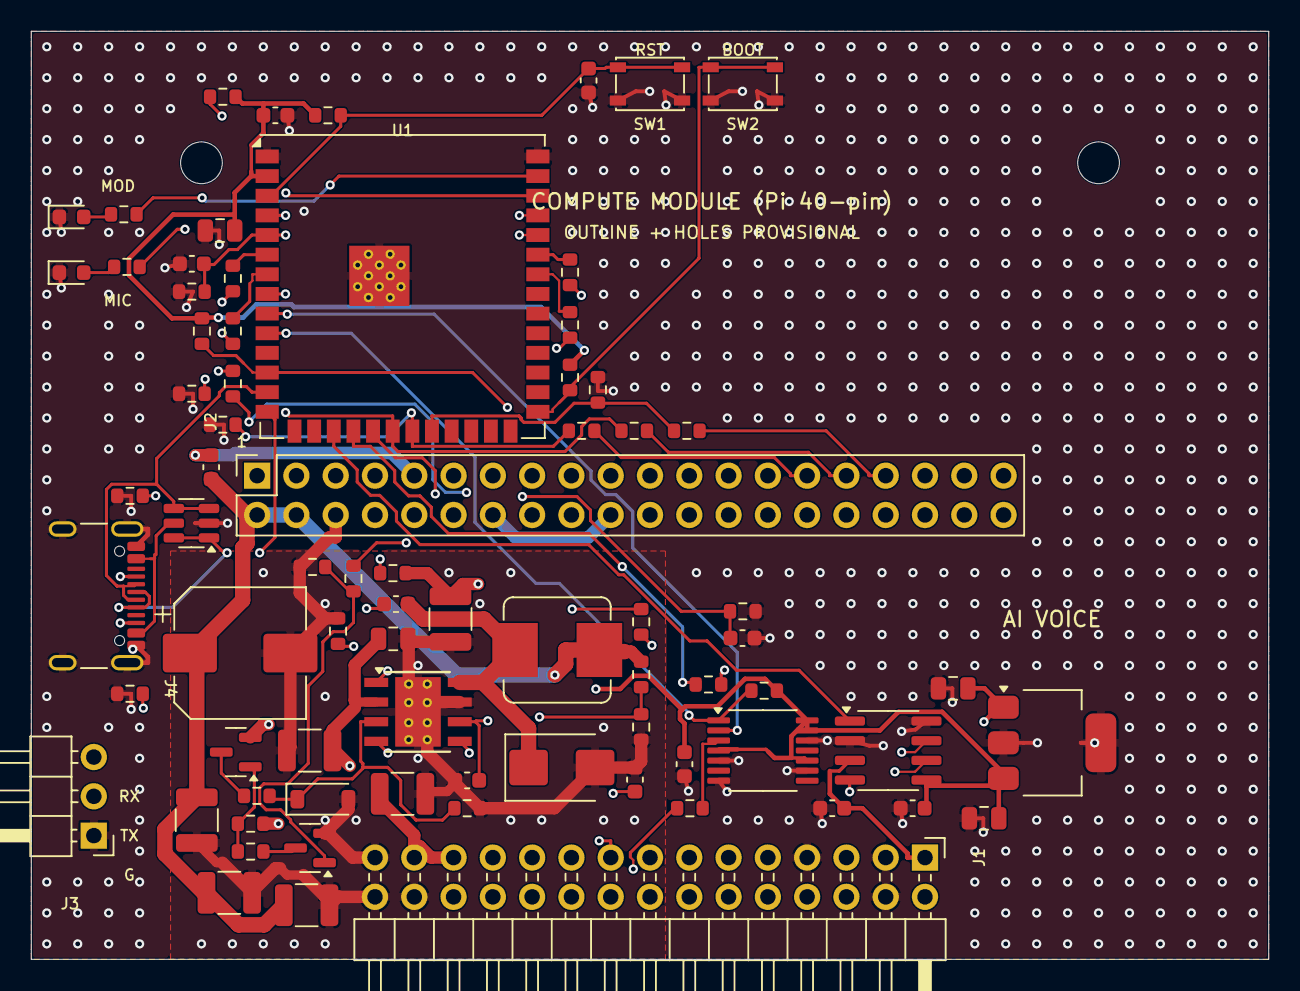
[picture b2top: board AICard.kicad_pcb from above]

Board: 4 copper layers, 80.0 x 60.0 mm, 78 parts (0 on the bottom side), 59 nets.

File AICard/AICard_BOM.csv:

Qty,Designators,Manufacturer part,Description,Package,Type,Side,Notes
1,C1,10u,U3 in,0805,SMD,Top,
2,C2 C3,22u,"U3 out; Module supply, at pin 2",0805,SMD,Top,
8,C4 C6 C7 C8 C10 C11 C12 C17,100n,"Module supply, at pin 2; U2 VDD; U2 VIO; U6 decoupling ...",0603,SMD,Top,
1,C5,1u,1u,0603,SMD,Top,
1,C9,"Panasonic EEE-FT1A471AP or equal (470 uF, 10 V, 8 x 10 mm, low ESR)","Bulk at the module's 5 V (CPU load steps): aluminium, 10 V or more, low ESR, 8 x 10 mm",CP_Elec_8x10,SMD,Top,
3,C13 C14 C15,2.2u 100V,"Buck input, at VIN (C1-C3 in the TI example)",1210,SMD,Top,
1,C16,100n,"Buck input, HF (100 V)",0805,SMD,Top,
3,C18 C19 C20,47u 10V,"Buck output (C6, C7, C9)",1210,SMD,Top,
1,C21,4.7n,Compensation (C5),0603,SMD,Top,
1,C22,47p,Compensation (C8),0603,SMD,Top,
1,D1,Module green,Compute module running,0603,SMD,Top,
1,D2,Mic amber,Microphone open,0603,SMD,Top,
1,D3,"Diodes B360B-13-F (3 A, 60 V Schottky, SMB)","Catch diode, 3 A 60 V Schottky, SMB",D_SMB,SMD,Top,
1,D4,"Nexperia BZT52C5V1 (5.1 V zener, SOD-123)","EN clamp, 5.1 V",D_SOD-123,SMD,Top,
2,H1 H2,M2.5 standoff + screw for the compute module (plain 2.7 mm holes in the card),M2.5,MountingHole_2.7mm_M2.5,Mech,Top,The hole positions are provisional until the module is measured
1,J1,"right-angle 2 x 15 pin header, 2.54 mm, 6 mm mating pins (e.g. Samtec TSW-115-08-G-D-RA)","Right-angle 2x15 header on the bottom edge (the slot pinout, docs/hardware/accessory_ports.md). Used: 5 V, GND, CAN, slot ID, I2S rail BCK / WS / MIC (inputs) and RET (a 3-state output), AUX 12 V / AUX GND (25-30). Not used: switched / constant 12 V, 3.3 V, WAKE, LAMP, REV, MCLK, audio bus",PinHeader_2x15_P2.54mm_Horizontal,THT,Top,
1,J2,"female 2 x 20 socket, 2.54 mm, 8.5 mm insulator (e.g. Sullins PPPC202LFBN-RC)","Female socket 2 x 20, 2.54 mm, 8.5 mm insulator: the compute module plugs in here. Raspberry Pi 40-pin pinout",PinSocket_2x20_P2.54mm_Vertical,THT,Top,The module itself is a separate part: Radxa Zero 3W 8 GB with eMMC (or a Pi-header compatible board). Not on the BOM
1,J3,"1 x 3 right-angle pin header, 2.54 mm","Right angle, left edge: GND, TX0 (to the adapter RX), RX0 (from the adapter TX). 3.3 V logic. Not a supply",PinHeader_1x03_P2.54mm_Horizontal,THT,Top,
1,J4,"GCT USB4105-GF-A (USB 2.0 Type-C, 16-pin, horizontal)","USB 2.0 Type-C receptacle, GCT USB4105-xx-A (16-pin, horizontal, top mount) on the left edge. Only the A4 / B9 VBUS contacts are wired (to the ESD clamp): VBUS powers nothing here, and A9 / B4 sit 4.8 mm away across the signal pads",USB_C_Receptacle_GCT_USB4105-xx-A_16P_TopMnt_Horizontal,SMD,Top,
1,L1,"Bourns SRP7028A-6R8M (Isat >= 5 A, Irms >= 3 A: check)","6.8 uH shielded, 7 x 7 mm, Isat >= 5 A, Irms >= 3 A (Bourns SRP7028A-6R8M or equal: check the ratings)",L_Bourns_SRP7028A_7.3x6.6mm,SMD,Top,
1,Q1,"Diodes DMP6350S-7 (P-FET, -60 V, SOT-23)","P-FET (60 V, SOT-23): connects AUX 12 V to the EN divider when its gate is pulled down by Q2. Vgs is limited by the 47k / 47k divider",SOT-23,SMD,Top,Q1: 60 V rating for load-dump on AUX 12 V; Vgs limited to half the supply by the 47k / 47k divider
1,Q2,"onsemi 2N7002 (N-FET, 60 V, SOT-23)",N-FET: GPIO11 high turns the module's buck on,SOT-23,SMD,Top,
4,R1 R2 R3 R24,10k,Slot ID pull-up (the main board has one resistor to GND per slot); 10k; NTC divider top,0603,SMD,Top,
2,R4 R5,5.1k,CC1 pull-down: the card is a USB device (sink); CC2 pull-down,0603,SMD,Top,
9,R6 R7 R8 R14 R15 R16 R18 R20 R30,1k,"Series R on the receive line, as on the DigiDash board; 1k; Link TX series (the module may be off); Link RX series ...",0603,SMD,Top,
3,R9 R10 R11,100,Series on the rail input BCK; Series on the rail input WS; Series on the rail input MIC,0603,SMD,Top,
5,R12 R17 R19 R21 R31,100k,RET buffer off until the firmware pulls GPIO17 low (the rail rule: off at power-up); ALIVE low when the module is off; SHUTDOWN_REQ low while the ESP32 resets; ATTN low when the module is off ...,0603,SMD,Top,
1,R13,33,RET series damping,0603,SMD,Top,
1,R22,220k,"AUX present divider top (on the AUX 12 V side, in the buck area)",0603,SMD,Top,
3,R23 R28 R29,47k,AUX present divider bottom; Q1 gate pull-up (off by default); Q1 gate pull-down through Q2: Vgs = half of AUX 12 V (7 V at 14.4 V),0603,SMD,Top,
1,R25,243k,RT: 400 kHz (R3),0603,SMD,Top,
1,R26,442k,EN divider top (R1): starts above about 6.5 V,0603,SMD,Top,
1,R27,90.9k,EN divider bottom (R2),0603,SMD,Top,
1,R32,53.6k,Feedback top (R5): 5.0 V,0603,SMD,Top,
1,R33,10.2k,Feedback bottom (R6),0603,SMD,Top,
1,R34,16.9k,Compensation (R4),0603,SMD,Top,
1,RT1,"Murata NCP18XH103F03RB (10k, beta 3950, 0603) or equal","Card thermistor, 10k at 25 C, beta 3950, 0603, beside the module's heat source",0603,SMD,Top,Beta 3950: the firmware converts with it (ai_pins.h AI_NTC_BETA)
1,SW1,C&K PTS810 SJM 250 SMTR LFS (SPST tactile),RESET,SW_SPST_PTS810,SMD,Top,
1,SW2,C&K PTS810 SJM 250 SMTR LFS (SPST tactile),BOOT,SW_SPST_PTS810,SMD,Top,
1,U1,"Espressif ESP32-S3-WROOM-1U-N16R8 (16 MB flash, 8 MB octal PSRAM, IPEX)","Espressif ESP32-S3-WROOM-1U-N16R8 (16 MB flash, 8 MB octal PSRAM), IPEX connector only (the radio is not used), so no antenna keep-out: it sits under the compute module",ESP32-S3-WROOM-1U,SMD,Top,
1,U2,Microchip MCP2562-E/SN,MCP2562-E/SN,SOIC-8_3.9x4.9mm_P1.27mm,SMD,Top,
1,U3,"Diodes AP7361C-33E-13 (3.3 V, 1 A LDO, SOT-223)","3.3 V 1 A LDO, from the slot 5 V",SOT-223-3_TabPin2,SMD,Top,
1,U4,ST USBLC6-2SC6,"USB ESD clamp on D+ / D-, at the connector",SOT-23-6,SMD,Top,
1,U5,TI TPS54560BDDAR,"5 V step-down, 4.5-60 V in, 5 A switch",TI_SO-PowerPAD-8_ThermalVias,SMD,Top,Same circuit as the main board and the LTE card; check the loop with the 470 uF and the real load
1,U6,Nexperia 74LVC125APW (TSSOP-14),"Quad buffer, 3-state (active-low enables): gate 1 drives RET. The other three gates are tied off",TSSOP-14_4.4x5mm_P0.65mm,SMD,Top,
